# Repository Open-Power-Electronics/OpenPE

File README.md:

<p align="center">
  <picture>
    <source media="(prefers-color-scheme: dark)" srcset="public/brand/openpe-lockup-dark.png">
    
  </picture>
</p>

<p align="center">

</p>

<p align="center">
  <a href="https://open-power-electronics.github.io/">Website</a> ·
  <a href="https://github.com/Open-Power-Electronics/OpenPE/releases">Download</a> ·
  <a href="docs/README.md">Documentation</a> ·
  <a href="CONTRIBUTING.md">Contributing</a>
</p>

<p align="center">
  <b>English</b> · <a href="README.zh-CN.md">简体中文</a>
</p>

OpenPE · Electrical Engineering Studio is an open-source desktop app for power-electronics design built on [native KiCad 10 project files](docs/FORMAT.md). The Agent conversation sits on the left. Schematic, PCB layout, Model and native Source sit on the right, in one local project.

OpenPE bundles OpenCASCADE, ngspice, Gmsh and Elmer. Manual editing and supported simulation work without an Agent. General KiCad import, complete ERC/DRC parity, autorouting and production qualification are outside the [supported scope](docs/README.md#coverage-and-limits).

## Highlights

<table>
  <tr>
    <td width="33%" valign="top">
      
      <p><b>Schematic and simulation.</b> Edit the circuit, draw custom symbols and run a supported ngspice transient.</p>
    </td>
    <td width="33%" valign="top">
      
      <p><b>PCB layout.</b> Place and route the board manually, draw custom footprints and inspect it in 3D.</p>
    </td>
    <td width="33%" valign="top">
      
      <p><b>Model CAD.</b> Create bounded CAD solids around the board and export enclosure STEP.</p>
    </td>
  </tr>
</table>

## Features

- **Native KiCad 10 files.** Edit `.kicad_pro`, `.kicad_sch` and `.kicad_pcb` in Source and save a portable project with its supporting assets. Save retains the bytes of unchanged native files.
- **Local checks and fabrication files.** Run read-only ERC and DRC and export supported Gerber X2, Excellon and board-outline DXF files without installing KiCad. See the [design rules](docs/DESIGN-RULES.md) and [export coverage](docs/FORMAT.md#manufacturing-export).
- **One project, three views.** Schematic, Layout and Model share one native project and one undo history.
- **Local Agents.** Discuss the open project and request edits from an Agent you already run.
- **Built-in analysis.** Simulation, board temperature, parasitics and EMC review run as plugins on the same project.
- **Local by default.** Manage independent projects and conversations, recover design drafts and compare local Git history.

## Agents

OpenPE connects to Agent runtimes you install separately. Access depends on the Agent:

| Agent | Access |
| --- | --- |
| Codex | Scoped tools on the open schematic, PCB layout, Model CAD and supported simulation |
| Claude Code | Scoped tools on the open schematic, PCB layout, Model CAD and supported simulation |
| Cursor | Scoped tools on the open schematic, PCB layout, Model CAD and supported simulation |
| DeepSeek Harness | Project context and proposals |
| Pi | Project context and proposals |

[Raw KiCad mode](DESIGN.md#settings-and-appearance) pauses the workbench and sends selected native files from a chat-only view. Projects stay on disk as native KiCad files. The provider you choose receives the prompts and context you send. See [Agent tools](docs/API.md#agent-tools).

## Built-in plugins

| Plugin | What it does | Limits |
| --- | --- | --- |
| [SPICE Simulation](docs/SIMULATION.md) | Runs supported transients and shows waveforms | Bundled ngspice 47; not production validation |
| [Layout Thermal](docs/THERMAL.md) | Estimates steady PCB temperature with Gmsh and Elmer | Board temperature, not junction temperature; no airflow model |
| [Layout Parasitics](docs/LAYOUT.md) | Measures two-terminal DC resistance and partial inductance | Same-net pads or vias; no return path |
| [EMC Analysis](docs/EMC.md) | Reviews PCB geometry for EMC risks and records reports | A design review, not an emission or compliance verdict |
| PE Layout Skill | Gives Agents power-electronics PCB design guidance | Guidance only; not an autorouter |

You can also install a local JavaScript plugin with declared inputs and optional project read access. See the [plugin SDK](docs/PLUGINS.md#plugin-packages-and-sdk).

## Install

| Platform | Installer | Status |
| --- | --- | --- |
| Windows x64 | `OpenPE-0.1.1-x64.exe` | v0.1.1 Beta, unsigned |
| macOS arm64 | `OpenPE-0.1.1-arm64.dmg` | v0.1.1 Beta, ad hoc signed, not notarized |
| Linux x64 | `OpenPE-0.1.1.AppImage` or `openpe_0.1.1_amd64.deb` | v0.1.1 Beta, Debian 13 or equivalent with glibc 2.41+ |

Download the installer for your platform from [Releases](https://github.com/Open-Power-Electronics/OpenPE/releases). All installers include ngspice, Gmsh and Elmer. See the [installation guide](docs/DEVELOPMENT.md#install-the-app) for first launch and host requirements.

### Run from source

Requires Node.js 24 and Git. On Linux x64, follow the [solver build steps](docs/DEVELOPMENT.md#maintainer-solver-builds) after `npm ci` and before `npm run dev`.

```sh
git clone https://github.com/Open-Power-Electronics/OpenPE.git
cd OpenPE
npm ci
npm run libraries:download
npm run dev
```

The [development guide](docs/DEVELOPMENT.md#run-from-source) also covers browser mode, offline solver preparation, checks and packaging.

## Documentation

| I want to | Read |
| --- | --- |
| Install or run OpenPE | [Setup and development](docs/DEVELOPMENT.md) |
| Know what is supported | [Coverage and limits](docs/README.md#coverage-and-limits) |
| Start from an example | [Examples](docs/EXAMPLES.md) |
| Edit PCB and Model geometry | [Layout and Model](docs/LAYOUT.md) |
| Run simulation or thermal analysis | [SPICE Simulation](docs/SIMULATION.md), [Layout Thermal](docs/THERMAL.md) |
| Review EMC | [EMC Analysis](docs/EMC.md) |
| Write a plugin | [Plugins](docs/PLUGINS.md) |
| Understand the system | [Architecture](docs/ARCHITECTURE.md) |
| Browse everything | [Documentation index](docs/README.md) |

## Contributing

Bug reports are welcome through [GitHub issues](https://github.com/Open-Power-Electronics/OpenPE/issues). Code changes currently come from the OpenPE core team. See [Contributing](CONTRIBUTING.md).

## Team

OpenPE is developed by contributors from leading universities around the world.

**Authors:** Xiao Yang · Yukang Zhu · Wenhao Deng · Tian Xia · Chengmin Li · Dongsheng Yang · Tailin Wu

**Universities:** University of California, Berkeley · University of California, Los Angeles · Massachusetts Institute of Technology · University of Glasgow · Eindhoven University of Technology · Westlake University

## Acknowledgements

OpenPE builds on KiCad file formats, ngspice, Open CASCADE, Gmsh and Elmer. Their notices are in [`public/licenses/`](public/licenses/).

## License

[Apache-2.0](LICENSE). Third-party assets retain their licenses and attribution.

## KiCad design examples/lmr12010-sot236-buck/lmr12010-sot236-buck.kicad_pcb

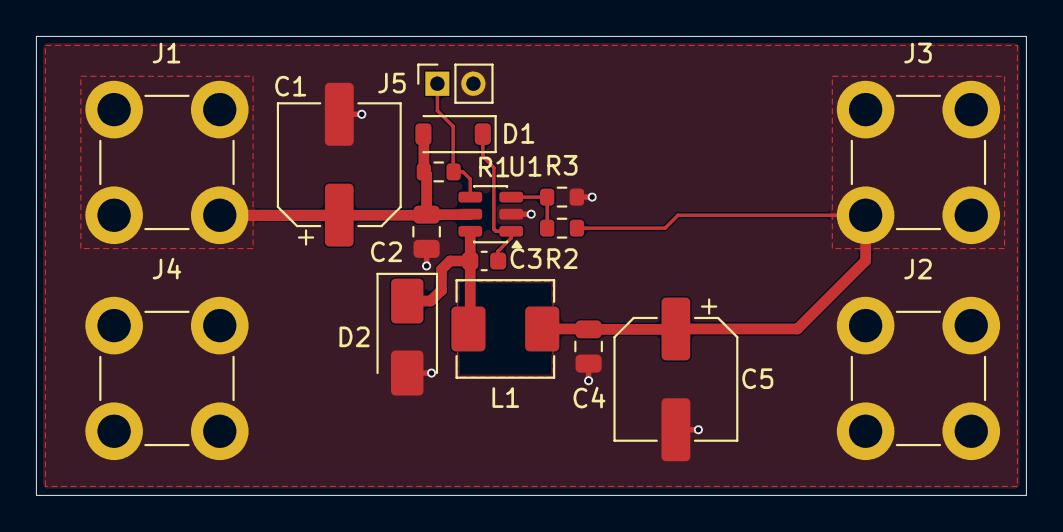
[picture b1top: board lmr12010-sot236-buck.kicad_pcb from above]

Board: 2 copper layers, 55.0 x 25.5 mm, 17 parts (0 on the bottom side), 7 nets.

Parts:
C1: 22uF; CP_Elec_6.3x5.3
C2, C4: 0.1uF; C_0805_2012Metric
C3: 0.1uF; C_0603_1608Metric
C5: 15uF; CP_Elec_6.3x5.3
D1: D_Filled; D_SOD-123
D2: D_Filled; D_SMA
J1, J2, J3, J4: Screw_Terminal_01x01; Wuerth_REDCUBE-THR_WP-THRSH_74651174_THR
J5: Conn_01x02; PinSocket_1x02_P2.00mm_Vertical
L1: 82uH; L_APV_APH0530
R1: 100k; R_0603_1608Metric
R2: 118k; R_0603_1608Metric
R3: 22.1k; R_0603_1608Metric
U1: LMR12010X; SOT-23-6

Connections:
/EN: J5.1, R1.2, U1.4
/VIN: C1.1, C2.2, D1.2, J1.1, R1.1, U1.5
/VOUT: C4.2, C5.1, J3.1, L1.1, R2.1
GND: C1.2, C2.1, C4.1, C5.2, D2.2, J2.1, J4.1, J5.2, R3.2, U1.2
unnamed: C3.1, D1.1, U1.1
unnamed: C3.2, D2.1, L1.2, U1.6
unnamed: R2.2, R3.1, U1.3

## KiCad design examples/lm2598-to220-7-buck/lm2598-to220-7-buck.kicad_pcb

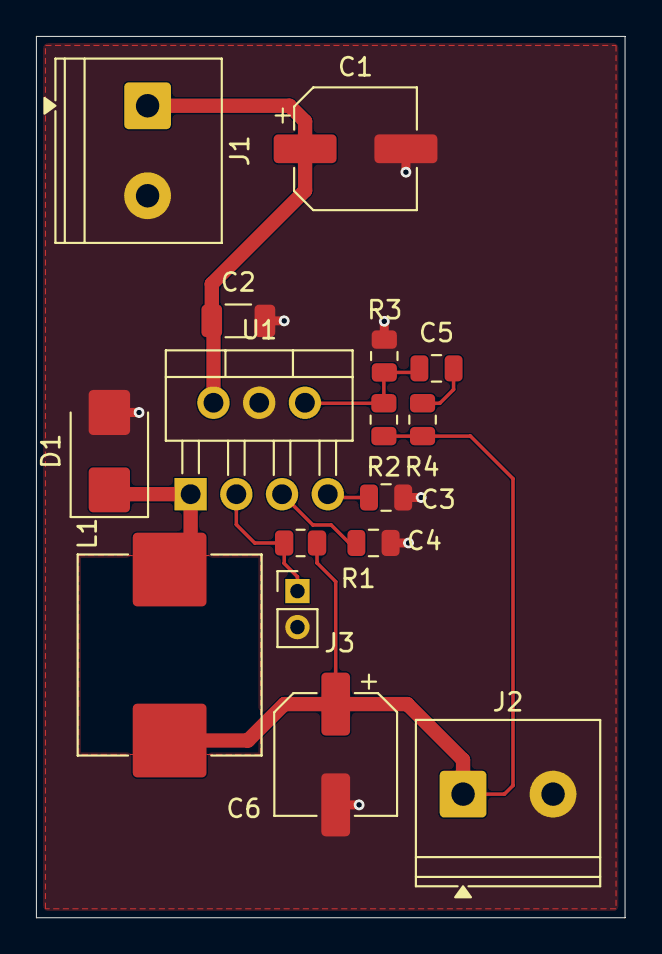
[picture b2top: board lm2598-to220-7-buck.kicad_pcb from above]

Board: 2 copper layers, 32.7 x 49.0 mm, 16 parts (0 on the bottom side), 9 nets.

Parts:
C1: 100uF; CP_Elec_6.3x5.2
C2: 10uF; C_1206_3216Metric
C3, C4: 0.1uF; C_0805_2012Metric
C5: 3.3nF; C_0805_2012Metric
C6: 220uF; CP_Elec_6.3x5.2
D1: D_Schottky; D_SMB
J1, J2: Conn_01x02; TerminalBlock_Phoenix_PT-1,5-2-5.0-H_1x02_P5.00mm_Horizontal
J3: Conn_01x02; PinHeader_1x02_P2.00mm_Vertical
L1: 33uH; L_Changjiang_FXL1050
R1: 4.7k; R_0805_2012Metric
R2: 7.1k; R_0805_2012Metric
R3: 1k; R_0805_2012Metric
R4: 3k; R_0805_2012Metric
U1: LM2598_ADJ; TO-220-7_P2.54x5.08mm_StaggerOdd_Lead3.08mm_Vertical

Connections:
/FLAG: J3.1, R1.1, U1.3
/VIN: C1.1, C2.1, J1.1, U1.2
/VOUT: C6.1, J2.1, L1.2, R1.2, R2.2, R4.2
GND: C1.2, C2.2, C3.2, C4.2, C6.2, D1.2, J1.2, J2.2, J3.2, R3.1, U1.4
unnamed: C5.2, R4.1
unnamed: D1.1, L1.1, U1.1
unnamed: C4.1, U1.5
unnamed: C5.1, R2.1, R3.2, U1.6
unnamed: C3.1, U1.7

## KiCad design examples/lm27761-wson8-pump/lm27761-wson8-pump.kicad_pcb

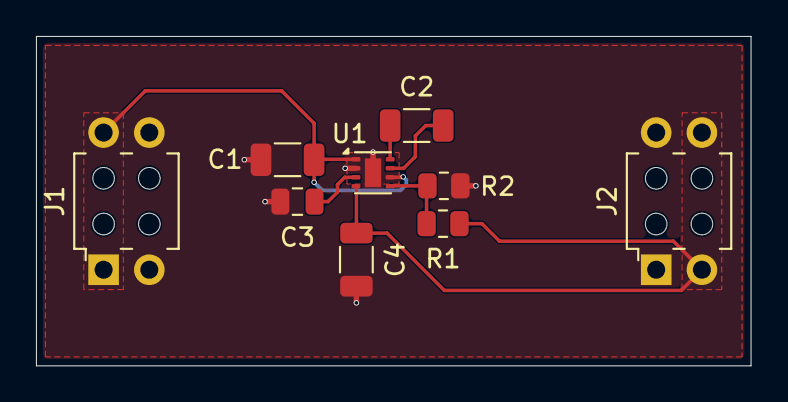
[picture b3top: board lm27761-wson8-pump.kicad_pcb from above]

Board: 2 copper layers, 39.7 x 18.3 mm, 9 parts (0 on the bottom side), 7 nets.

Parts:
C1, C4: 2.2uF; C_1206_3216Metric
C2: 1uF; C_1206_3216Metric
C3: 4.7uF; C_0805_2012Metric
J1, J2: Conn_02x02_Top_Bottom; Wuerth_WR-PHD_613004216921_Large_2x02_P2.54mm_Vertical
R1: 17.4k; R_0805_2012Metric
R2: 10.2k; R_0805_2012Metric
U1: LM27761; WSON-8-1EP_2x2mm_P0.5mm_EP0.9x1.6mm

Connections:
/VIN: C1.1, J1.1, J1.2, U1.1, U1.6
/VOUT: C4.1, J2.3, J2.4, R1.1, U1.4
GND: C1.2, C3.2, C4.2, J1.3, J1.4, J2.1, J2.2, R2.2, U1.2, U1.9
unnamed: C2.1, U1.8
unnamed: C2.2, U1.7
unnamed: C3.1, U1.3
unnamed: R1.2, R2.1, U1.5

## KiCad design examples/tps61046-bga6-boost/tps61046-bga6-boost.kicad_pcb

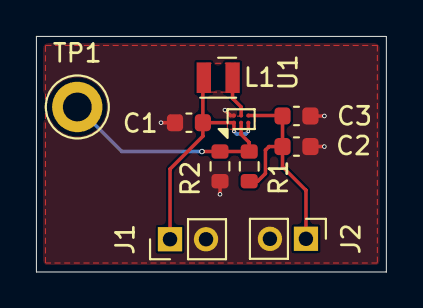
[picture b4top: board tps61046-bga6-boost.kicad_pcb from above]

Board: 2 copper layers, 19.4 x 13.1 mm, 10 parts (0 on the bottom side), 5 nets.

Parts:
C1, C2, C3: 10uF; C_0603_1608Metric
J1, J2: Conn_01x02; PinHeader_1x02_P2.00mm_Vertical
L1: 2.2uH; L_Wurth_WE-LQSH-2010
R1: 232k; R_0603_1608Metric
R2: 10.2k; R_0603_1608Metric
TP1: TestPoint; TestPoint_Keystone_5005-5009_Compact
U1: TPS61046; Texas_DSBGA-6_0.855x1.255mm_Layout2x3_P0.4mm_LevelC

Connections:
/VIN: C1.1, J1.1, L1.1, U1.A1, U1.C1
/VOUT: C2.2, C3.2, J2.1, R1.1, U1.C2
GND: C1.2, C2.1, C3.1, J1.2, J2.2, R2.2, U1.A2
unnamed: R1.2, R2.1, TP1.1, U1.B1
unnamed: L1.2, U1.B2

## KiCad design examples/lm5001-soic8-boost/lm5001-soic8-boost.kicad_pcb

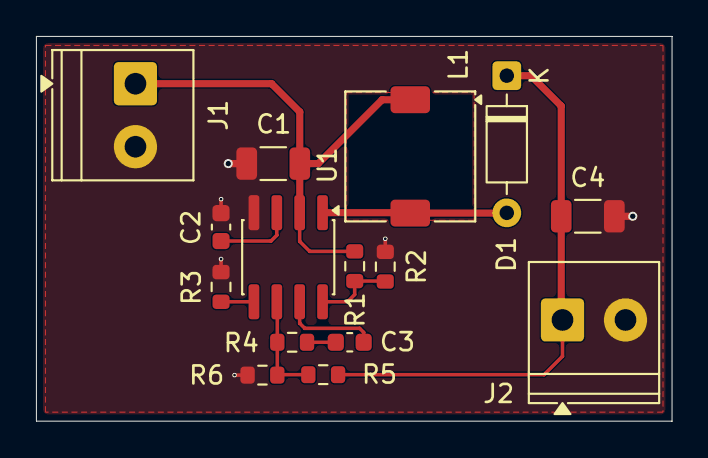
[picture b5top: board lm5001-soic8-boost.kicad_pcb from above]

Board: 2 copper layers, 35.3 x 21.4 mm, 15 parts (0 on the bottom side), 10 nets.

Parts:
C1: 4.7uF; C_1206_3216Metric
C2: 1uF; C_0603_1608Metric
C3: 2.2uF; C_0603_1608Metric
C4: 10uF; C_1206_3216Metric
D1: 1N4149; D_DO-35_SOD27_P7.62mm_Horizontal
J1, J2: Conn_01x02; TerminalBlock_Phoenix_PT-1,5-2-3.5-H_1x02_P3.50mm_Horizontal
L1: 100uH; L_TDK_SLF7055
R1: 60.4k; R_0603_1608Metric
R2: 6.04k; R_0603_1608Metric
R3: 52.3k; R_0603_1608Metric
R4: 73.2k; R_0603_1608Metric
R5: 54.9k; R_0603_1608Metric
R6: 1.47k; R_0603_1608Metric
U1: LM5001; SOIC-8_3.9x4.9mm_P1.27mm

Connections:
/VIN: C1.1, J1.1, L1.1, R1.2, U1.2
/VOUT: C4.1, D1.1, J2.1, R5.2
GND: C1.2, C2.1, C4.2, J1.2, J2.2, R2.1, R3.1, R6.1, U1.4
unnamed: C3.1, R4.2
unnamed: D1.2, L1.2, U1.1
unnamed: C3.2, U1.7
unnamed: R1.1, R2.2, U1.8
unnamed: R4.1, R5.1, R6.2, U1.6
unnamed: R3.2, U1.5
unnamed: C2.2, U1.3

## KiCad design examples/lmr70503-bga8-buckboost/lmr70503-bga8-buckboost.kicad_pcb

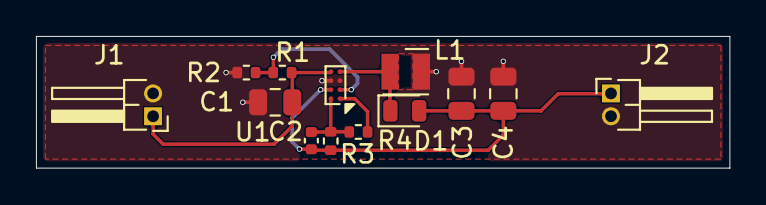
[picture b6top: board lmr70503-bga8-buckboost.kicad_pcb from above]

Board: 2 copper layers, 38.5 x 7.3 mm, 13 parts (0 on the bottom side), 7 nets.

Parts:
C1: 10uF; C_0805_2012Metric
C2: 47pF; C_0402_1005Metric
C3, C4: 22uF; C_0805_2012Metric
D1: D; D_MicroMELF
J1, J2: Conn_01x02; PinHeader_1x02_P1.27mm_Horizontal
L1: 1uH; L_Wurth_WE-LQSH-2512
R1, R2: 511k; R_0402_1005Metric
R3: 300k; R_0402_1005Metric
R4: 91k; R_0402_1005Metric
U1: LMR70503; Texas_DSBGA-8_0.9x1.9mm_Layout2x4_P0.5mm

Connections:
/VIN: C1.1, J1.1, R1.1, U1.D2
/VOUT: C2.2, C3.1, C4.1, D1.2, J2.1, R3.1, U1.B2
GND: C1.2, C3.2, C4.2, J1.2, J2.2, L1.2, R2.2, U1.C1, U1.C2
unnamed: D1.1, L1.1, U1.D1
unnamed: R1.2, R2.1, U1.B1
unnamed: C2.1, R3.2, R4.1, U1.A2
unnamed: R4.2, U1.A1

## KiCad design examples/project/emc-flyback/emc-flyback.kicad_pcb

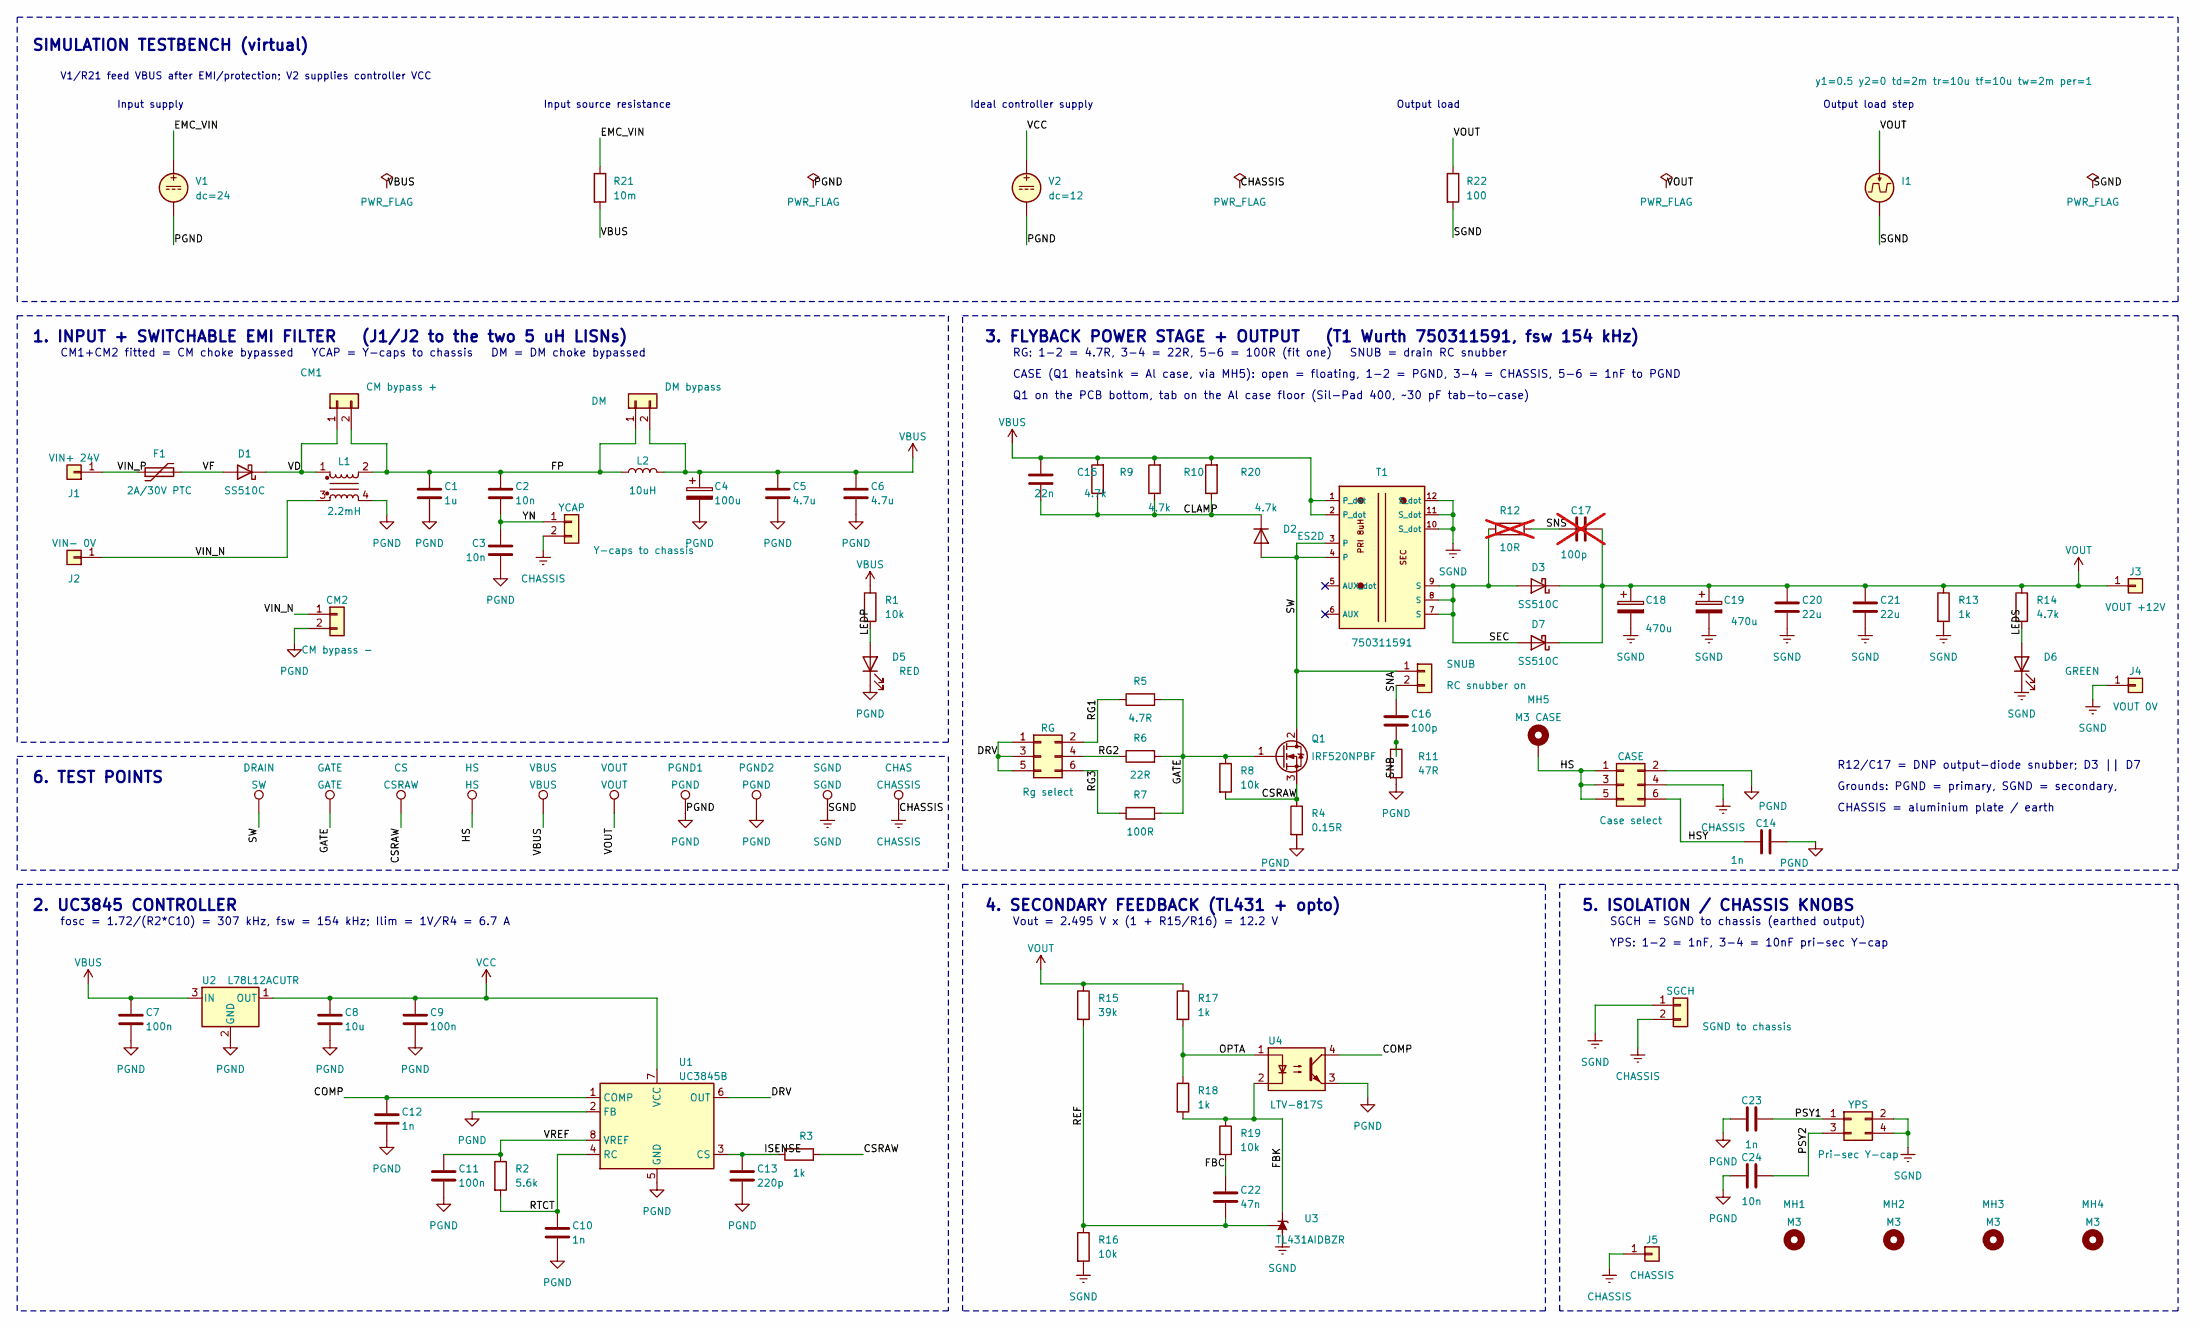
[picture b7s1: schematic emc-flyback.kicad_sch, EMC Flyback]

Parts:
C1: 1u; C_1206_3216Metric; MPN CL31B105KBHNNNE; LCSC C1848
C2, C3, C24: 10n; C_1206_3216Metric; MPN CC1206KKX7RCBB103; LCSC C107192
C4: 100u; CP_Elec_10x10; MPN MVK 50V100 M 10*10; LCSC C165627
C5, C6: 4.7u; C_1210_3225Metric; MPN CL32B475KBUYNNE; LCSC C170099
C7, C9, C11: 100n; C_0603_1608Metric; MPN CC0603KRX7R9BB104; LCSC C14663
C8: 10u; C_0805_2012Metric; MPN CL21A106KAYNNNE; LCSC C15850
C10: 1n; C_0603_1608Metric; MPN CL10C102JB8NNNC; LCSC C163508
C12: 1n; C_0603_1608Metric; MPN CL10B102KB8NNNC; LCSC C1588
C13: 220p; C_0603_1608Metric; MPN CL10B221KB8NNNC; LCSC C1603
C14, C23: 1n; C_1206_3216Metric; MPN CC1206KKX7RDBB102; LCSC C23631
C15: 22n; C_0805_2012Metric; MPN CC0805KRX7R0BB223; LCSC C107137
C16: 100p; C_1206_3216Metric; MPN TCC1206COG101J202DT; LCSC C2833637
C17: 100p; C_1206_3216Metric; MPN TCC1206COG101J202DT; LCSC C2833637; not fitted
C18, C19: 470u; CP_Elec_10x10; MPN RVT1E471M1010; LCSC C72518
C20, C21: 22u; C_1210_3225Metric; MPN CL32A226KAJNNNE; LCSC C52306
C22: 47n; C_0603_1608Metric; MPN CL10B473KB8NNNC; LCSC C1622
CASE: Case select; PinHeader_2x03_P2.54mm_Vertical; MPN PZ254V-12-6P; LCSC C492420
CHAS: CHASSIS; TestPoint_Keystone_5000-5004_Miniature; MPN Keystone 5001 (black); LCSC C238122
CM1: CM bypass +; PinHeader_1x02_P2.54mm_Vertical; MPN PZ254V-11-02P; LCSC C492401
CM2: CM bypass -; PinHeader_1x02_P2.54mm_Vertical; MPN PZ254V-11-02P; LCSC C492401
CS: CSRAW; TestPoint_Keystone_5000-5004_Miniature; MPN Keystone 5002 (white); LCSC C238123
D1: SS510C; D_SMC; MPN SS510C (reverse-polarity); LCSC C19229
D2: ES2D; D_SMA; MPN ES2D; LCSC C364267
D3, D7: SS510C; D_SMC; MPN SS510C; LCSC C19229
D5: RED; LED_0805_2012Metric; MPN NCD0805R1; LCSC C84256
D6: GREEN; LED_0805_2012Metric; MPN KT-0805G; LCSC C2297
DM: DM bypass; PinHeader_1x02_P2.54mm_Vertical; MPN PZ254V-11-02P; LCSC C492401
DRAIN: SW; TestPoint_Keystone_5000-5004_Miniature; MPN Keystone 5002 (white); LCSC C238123
F1: 2A/30V PTC; Fuse_1812_4532Metric; MPN BSMD1812-200-30V; LCSC C960026
GATE: GATE; TestPoint_Keystone_5000-5004_Miniature; MPN Keystone 5002 (white); LCSC C238123
HS: HS; TestPoint_Keystone_5000-5004_Miniature; MPN Keystone 5002 (white); LCSC C238123
I1: y1=0.5 y2=0 td=2m tr=10u tf=10u tw=2m per=1
J1: VIN+ 24V; Jack_4mm_RA_Cliff_FCR7350; MPN Cliff FCR7350R (red), 4 mm right-angle 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
J2: VIN- 0V; Jack_4mm_RA_Cliff_FCR7350; MPN Cliff FCR7350B (black), 4 mm right-angl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
J3: VOUT +12V; Jack_4mm_RA_Cliff_FCR7350; MPN Cliff FCR7350R (red), 4 mm right-angle 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
J4: VOUT 0V; Jack_4mm_RA_Cliff_FCR7350; MPN Cliff FCR7350B (black), 4 mm right-angl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
J5: CHASSIS; Jack_4mm_RA_Cliff_FCR7350; MPN Cliff FCR7350G (green), 4 mm right-angl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
L1: 2.2mH; L_CommonMode_Wuerth_WE-CMB-S_744822222; MPN Wurth 744822222 (2.2 mH, 2 A)
L2: 10uH; L_Bourns-SRN8040_8x8.15mm; MPN SWPA8040S100MT; LCSC C37429
MH1, MH2, MH3, MH4: M3; MountingHole_3.2mm_M3
MH5: M3 CASE; MountingHole_3.2mm_M3_Pad_Via; MPN M3 x 8 mm metal hex stand-off (female-f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
PGND1, PGND2: PGND; TestPoint_Keystone_5000-5004_Miniature; MPN Keystone 5001 (black); LCSC C238122
Q1: IRF520NPBF; TO-220-3_BottomMount_CaseHeatsink; MPN IRF520NPBF (Infineon); LCSC C2598
R1, R8, R16, R19: 10k; R_0603_1608Metric; MPN 0603WAF1002T5E; LCSC C25804
R2: 5.6k; R_0603_1608Metric; MPN 0603WAF5601T5E; LCSC C23189
R3, R17, R18: 1k; R_0603_1608Metric; MPN 0603WAF1001T5E; LCSC C21190
R4: 0.15R; R_2512_6332Metric; MPN HoLR2512-150mR-1%; LCSC C500726
R5: 4.7R; R_0805_2012Metric; MPN 0805W8F470KT5E; LCSC C17675
R6: 22R; R_0805_2012Metric; MPN 0805W8F220JT5E; LCSC C17561
R7: 100R; R_0805_2012Metric; MPN 0805W8F1000T5E; LCSC C17408
R9, R10, R20: 4.7k; R_2512_6332Metric; MPN 25121WJ0472T4E (UNI-ROYAL)
R11: 47R; R_0805_2012Metric; MPN 0805W8F470JT5E; LCSC C17714
R12: 10R; R_1206_3216Metric; MPN 1206W4F100JT5E; LCSC C17903; not fitted
R13: 1k; R_1206_3216Metric; MPN 1206W4F1001T5E; LCSC C4410
R14: 4.7k; R_0603_1608Metric; MPN 0603WAF4701T5E; LCSC C23162
R15: 39k; R_0603_1608Metric; MPN 0603WAF3902T5E; LCSC C23153
R21: 10m
R22: 100
RG: Rg select; PinHeader_2x03_P2.54mm_Vertical; MPN PZ254V-12-6P; LCSC C492420
SGCH: SGND to chassis; PinHeader_1x02_P2.54mm_Vertical; MPN PZ254V-11-02P; LCSC C492401
SGND: SGND; TestPoint_Keystone_5000-5004_Miniature; MPN Keystone 5001 (black); LCSC C238122
SNUB: RC snubber on; PinHeader_1x02_P2.54mm_Vertical; MPN PZ254V-11-02P; LCSC C492401
T1: 750311591; Wurth_750311591_EFD25; MPN Wurth 750311591 (8 uH, 1.5:1:0.67, EFD2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
U1: UC3845B; SOIC-8_3.9x4.9mm_P1.27mm; MPN UC3845BD1013TR; LCSC C7118
U2: L78L12ACUTR; SOT-89-3; MPN L78L12ACUTR; LCSC C69601
U3: TL431AIDBZR; SOT-23; MPN TL431AIDBZR; LCSC C23892
U4: LTV-817S; SMDIP-4_W9.53mm; MPN LTV-817S; LCSC C189217
V1: dc=24
V2: dc=12
VBUS: VBUS; TestPoint_Keystone_5000-5004_Miniature; MPN Keystone 5002 (white); LCSC C238123
VOUT: VOUT; TestPoint_Keystone_5000-5004_Miniature; MPN Keystone 5002 (white); LCSC C238123
YCAP: Y-caps to chassis; PinHeader_1x02_P2.54mm_Vertical; MPN PZ254V-11-02P; LCSC C492401
YPS: Pri-sec Y-cap; PinHeader_2x02_P2.54mm_Vertical; MPN PZ254V-12-4P; LCSC C492419

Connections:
AUX_A: T1.5 (AUX_dot)
AUX_B: T1.6 (AUX)
CHASSIS: CASE.4, CHAS.1, J5.1, SGCH.2, YCAP.2
CLAMP: C15.1, D2.1 (K), R9.1, R10.1, R20.1
COMP: C12.1, U1.1 (COMP), U4.4
CSRAW: CS.1, Q1.3 (S), R3.1, R4.1, R8.2
DRV: RG.1, RG.3, RG.5, U1.6 (OUT)
FBC: C22.1, R19.2
FBK: R18.2, R19.1, U3.1 (K), U4.2
FP: C1.1, C2.1, CM1.2, DM.1, L1.2, L2.1
GATE: GATE.1, Q1.1 (G), R5.2, R6.2, R7.2, R8.1
HS: CASE.1, CASE.3, CASE.5, HS.1, MH5.1
HSY: C14.1, CASE.6
ISENSE: C13.1, R3.2, U1.3 (CS)
LEDP: D5.2 (A), R1.2
LEDS: D6.2 (A), R14.2
unnamed: R21.1, V1.1
OPTA: R17.2, R18.1, U4.1
PGND: C1.2, C3.2, C4.2, C5.2, C6.2, C7.2, C8.2, C9.2, C10.2, C11.2, C12.2, C13.2, C14.2, C23.1, C24.1, CASE.2, CM2.2, D5.1 (K), L1.4, PGND1.1, PGND2.1, R4.2, R11.2, U1.2 (FB), U1.5 (GND), U2.2 (GND), U4.3, V1.2, V2.2
PSY1: C23.2, YPS.1
PSY2: C24.2, YPS.3
REF: C22.2, R15.2, R16.1, U3.2 (REF)
RG1: R5.1, RG.2
RG2: R6.1, RG.4
RG3: R7.1, RG.6
RTCT: C10.1, R2.2, U1.4 (RC)
SEC: D3.2 (A), D7.2 (A), R12.1, T1.7 (S), T1.8 (S), T1.9 (S)
SGND: C18.2, C19.2, C20.2, C21.2, D6.1 (K), I1.2, J4.1, R13.2, R16.2, R22.2, SGCH.1, SGND.1, T1.10 (S_dot), T1.11 (S_dot), T1.12 (S_dot), U3.3 (A), YPS.2, YPS.4
SNA: C16.1, SNUB.2
SNB: C16.2, R11.1
SNS: C17.1, R12.2
SW: D2.2 (A), DRAIN.1, Q1.2 (D), SNUB.1, T1.3, T1.4
VBUS: C4.1, C5.1, C6.1, C7.1, C15.2, DM.2, L2.2, R1.1, R9.2, R10.2, R20.2, R21.2, T1.1 (P_dot), T1.2 (P_dot), U2.3 (IN), VBUS.1
VCC: C8.1, C9.1, U1.7 (VCC), U2.1 (OUT)
VD: CM1.1, D1.1 (K), L1.1
VF: D1.2 (A), F1.2
VIN_N: CM2.1, J2.1, L1.3
VIN_P: F1.1, J1.1
VOUT: C17.2, C18.1, C19.1, C20.1, C21.1, D3.1 (K), D7.1 (K), I1.1, J3.1, R13.1, R14.1, R15.1, R17.1, R22.1, VOUT.1
VREF: C11.1, R2.1, U1.8 (VREF)
YN: C2.2, C3.1, YCAP.1

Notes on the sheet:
R12/C17 = DNP output-diode snubber; D3 || D7
fosc = 1.72/(R2*C10) = 307 kHz, fsw = 154 kHz; Ilim = 1V/R4 = 6.7 A
CHASSIS = aluminium plate / earth
Grounds: PGND = primary, SGND = secondary,
4. SECONDARY FEEDBACK (TL431 + opto)
2. UC3845 CONTROLLER
1. INPUT + SWITCHABLE EMI FILTER (J1/J2 to the two 5 uH LISNs)
Vout = 2.495 V x (1 + R15/R16) = 12.2 V
6. TEST POINTS
3. FLYBACK POWER STAGE + OUTPUT (T1 Wurth 750311591, fsw 154 kHz)
YPS: 1-2 = 1nF, 3-4 = 10nF pri-sec Y-cap
SGCH = SGND to chassis (earthed output)
CASE (Q1 heatsink = Al case, via MH5): open = floating, 1-2 = PGND, 3-4 = CHASSIS, 5-6 = 1nF to PGND
5. ISOLATION / CHASSIS KNOBS
RG: 1-2 = 4.7R, 3-4 = 22R, 5-6 = 100R (fit one) SNUB = drain RC snubber
CM1+CM2 fitted = CM choke bypassed YCAP = Y-caps to chassis DM = DM choke bypassed
Q1 on the PCB bottom, tab on the Al case floor (Sil-Pad 400, ~30 pF tab-to-case)
SIMULATION TESTBENCH (virtual)
V1/R21 feed VBUS after EMI/protection; V2 supplies controller VCC
Input supply
Input source resistance
Ideal controller supply
Output load
Output load step

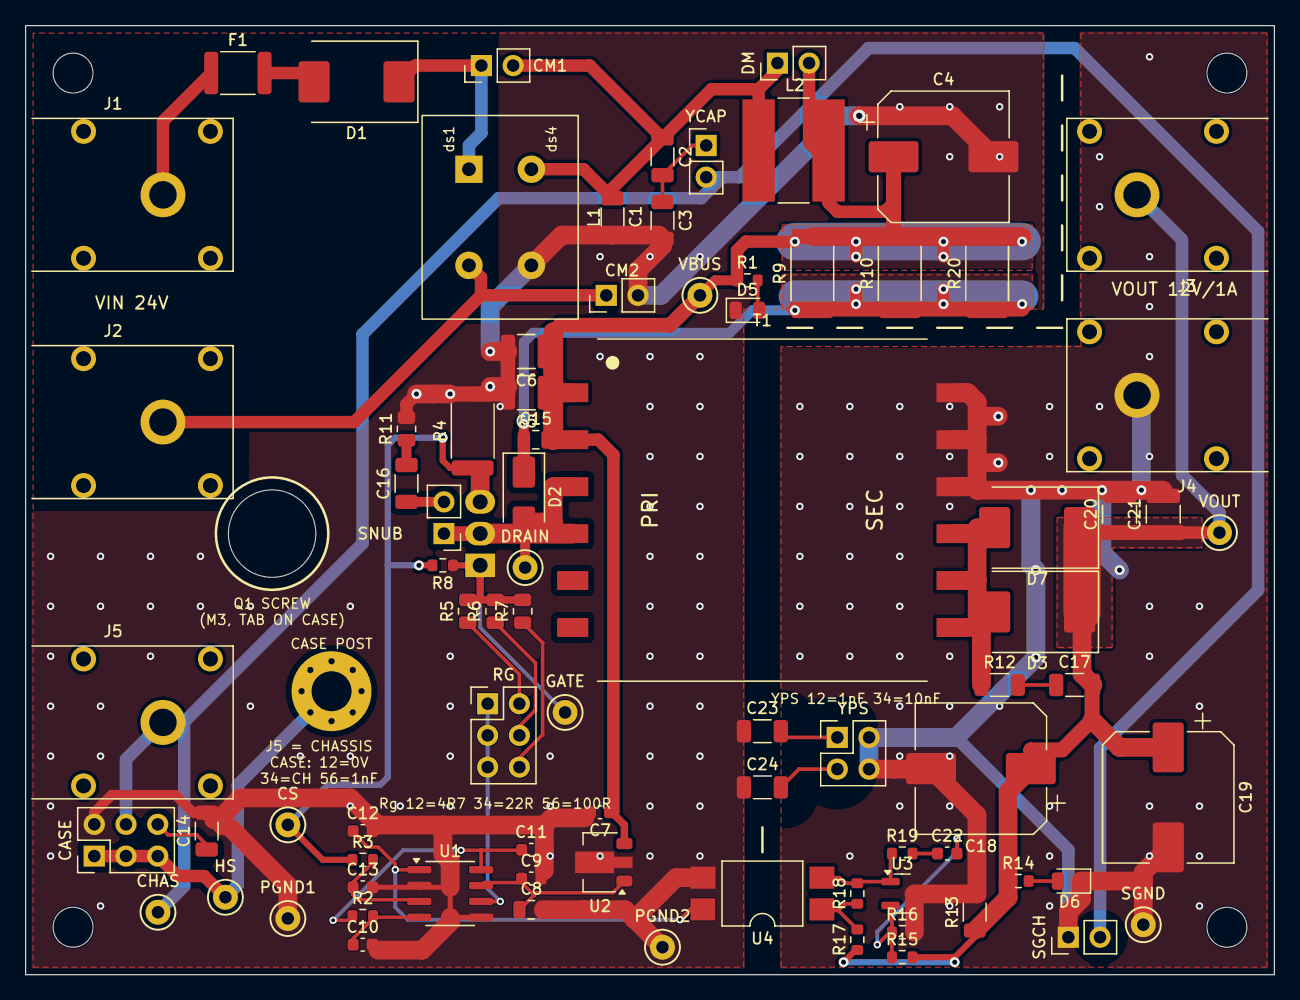
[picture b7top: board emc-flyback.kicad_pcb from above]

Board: 2 copper layers, 100.0 x 76.0 mm, 88 parts (0 on the bottom side), 38 nets.

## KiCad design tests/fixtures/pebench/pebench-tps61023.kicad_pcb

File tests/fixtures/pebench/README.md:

# PEBench regression fixtures

These ten source-derived designs are internal schematic/PCB regression fixtures, excluded from the Home catalog and application bundles. Home has nine curated Examples and the initial EMC Flyback Recent entry; see [Home projects](../../../docs/EXAMPLES.md). Each current structured `.openpe.json` contains an editable schematic, embedded symbols and PCB Layout; adjacent `.kicad_sch` / `.kicad_pcb` files are native KiCad 10 exports generated by the application's serializers. These build-only converters do not provide a general EAGLE or PCB importer in the workbench.

| Fixture              | Original designer | Copper layers | Hardware-document license |
| -------------------- | ----------------- | ------------- | ------------------------- |
| Sunny Buddy          | SparkFun          | 2             | CC BY-SA 4.0              |
| Buck-Boost TPS63070  | SparkFun          | 2             | CC BY-SA 4.0              |
| Buck AP63357         | SparkFun          | 4             | CC BY-SA 4.0              |
| Big Easy Driver      | SparkFun          | 4             | CC BY-SA 3.0              |
| Dual TB6612FNG       | SparkFun          | 2             | CC BY-SA 4.0              |
| PowerBoost 1000C     | Adafruit          | 2             | CC BY-SA 3.0              |
| Motor Shield V2      | Adafruit          | 2             | CC BY-SA 3.0              |
| DRV8871 Motor Driver | Adafruit          | 2             | CC BY-SA 3.0              |
| MiniBoost TPS61023   | Adafruit          | 2             | CC BY-SA 3.0              |
| AutoDriver L6470     | SparkFun          | 4             | CC BY-SA 4.0              |

[Manifest](manifest.json) pins repositories, commits, original source paths and SHA-256 hashes. [Source index](upstream-index.json) retains PEBench collection identities and source-provided acceptance/DRC records. Original EAGLE schematics/boards, PEBench-converted KiCad boards, source audits and notices are under [`upstream/`](upstream/). Conversion leaves those bytes unchanged, including `upstream-README.md` and license files. Derived documents retain the individual hardware licenses, independently of OpenPE's software license. [Combined attribution](licenses/NOTICE.txt) and the full [CC BY-SA 3.0](licenses/CC-BY-SA-3.0.txt) / [CC BY-SA 4.0](licenses/CC-BY-SA-4.0.txt) texts are retained locally.

These are educational design references, not qualified zero-DRC benchmark samples. Retained source acceptance/DRC records disclose existing limitations; conversion does not issue new approval. No production validation, ERC/DRC result or PEBench simulation profile is claimed. They are outside the Home/KiCad/TI real-solver sweep.

Fixtures share ordinary [Core](../../../docs/CORE.md) transactions, undo and
Source/revision gates. This does not expand model/import support. The
[fixture overview](../README.md#core-and-capability-checks) separates synthetic
transport coverage from native/solver evidence.

## Reproduce

From the OpenPE repository, with Python 3 and installed Node dependencies:

```sh
python scripts/pebench-schematic.py
node --import tsx scripts/build-pebench-examples.ts
```

The Python converter reads the ten pinned local sources and writes `converted/*.kicad_sch` plus conversion audits under `tests/fixtures/pebench/`. `scripts/pebench-schematic.py --collect <PEBench-directory>` is a separate, explicit source-collection step; ordinary regeneration does not read another checkout or use the network. Canonical generation verifies original schematic/board/converted-board hashes and the schematic audit's source hash, then uses deterministic IDs and the current validated project serializer. It writes individual fixture JSON/native exports, [`conversion-audit.json`](conversion-audit.json), the manifest and local notices. It does not update the application catalog. `npm run fixtures:generate` regenerates RC/KiCad/TI fixtures only; PEBench uses these dedicated steps. Do not hand-edit generated snapshots or pinned inputs.

Schematic conversion preserves EAGLE wire geometry, device/gate mappings and physical pad connectivity, with source labels attached to their actual segments. Filled curved artwork polygons are tessellated within 0.005 mm; adjacent artwork rectangles are merged exactly. EAGLE NC pins that are explicitly wired retain those wires through passive KiCad pins. These presentation/electrical-type changes are recorded in `converted/*.audit.json`; they are not an ERC equivalence claim. Source captions and licenses remain embedded.

PCB conversion preserves physical placement, pad shapes/numbers/nets, copper layers, tracks, vias, technical artwork and zone boundaries/settings. The converter omits cached zone fills. OpenPE provides bounded manual copper-zone filling, but it does not implement full KiCad rule parity or DRC. Refill and check native boards in KiCad before manufacturing; viewing/saving does not regenerate fills. Supported geometry remains editable and exports through the validated serializer. See [LAYOUT.md](../../../docs/LAYOUT.md) for preservation, fill and routing boundaries.

## Verification

```sh
npm test -- tests/pebench-pcb.test.ts
<KiCad-10-Python> scripts/check-pebench-kicad.py --cli <KiCad-10-CLI>
```

The unit check exercises build-only conversion, native preservation and editable geometry. The native command requires KiCad 10's Python with `pcbnew` and its matching CLI. It exports schematic netlists and compares physical pin groups against the original EAGLE XML, then reopens source/export boards to compare pads/drills/masks/nets/layers, tracks/vias/stacks, board/package artwork/text/captions and zone boundaries/holes/keepouts/thermal/island settings. Equivalent text angles are normalized. Linked Reference/Value captions follow the schematic while retaining source layout; ordinary native text macros remain intact. It also exports schematic/board SVGs.

Detailed native results go to `test-results/pebench-kicad/`; a complete ten-fixture pass records actual version/counts in [verification.json](verification.json). The committed record identifies **KiCad 10.0.1** and structural/connectivity scope. It is not a fresh check of later changes and does not establish ERC/DRC, simulation or manufacturing readiness. No simulation model preparation is required for these PCB regressions. Desktop checks require an explicit user request. Documentation-only edits need static checks rather than conversion or native/desktop execution.

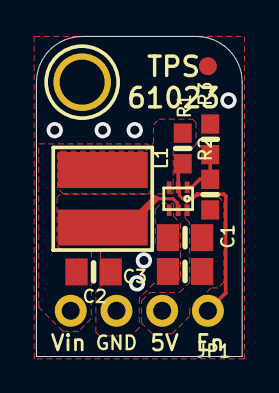
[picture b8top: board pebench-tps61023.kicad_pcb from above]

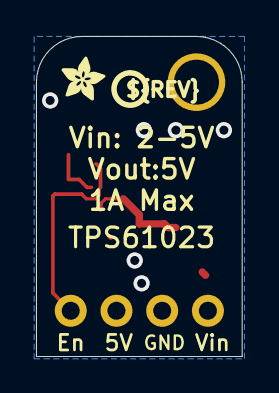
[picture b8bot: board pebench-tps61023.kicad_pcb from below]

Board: 2 copper layers, 11.4 x 17.8 mm, 13 parts (2 on the bottom side), 6 nets.

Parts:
C1, C2, C3: 22uF; 0805-NO
FID1: FIDUCIAL_1MM
IC1: TPS61023; SOT563
JP1: HEADER-1X4ROUND; 1X04_ROUND
L1: 1uH; INDUCTOR_5X5MM_TDK_VLC5045
R1, R3: 100K; 0603-NO
R2: 732K; 0603-NO
U$9: MOUNTINGHOLE2.5; MOUNTINGHOLE_2.5_PLATED
U$10: PCBFEAT-REV-040
U$11: ADAFRUIT_2.5MM

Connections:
EN: IC1.2, JP1.1, R1.2
FB: IC1.1, R2.2, R3.1
GND: C1.2, C2.2, C3.2, IC1.4, JP1.3, R3.2
SW: IC1.5, L1.P$2
VDD: C1.1, C3.1, IC1.6, JP1.2, R2.1
VIN: C2.1, IC1.3, JP1.4, L1.P$1, R1.1
